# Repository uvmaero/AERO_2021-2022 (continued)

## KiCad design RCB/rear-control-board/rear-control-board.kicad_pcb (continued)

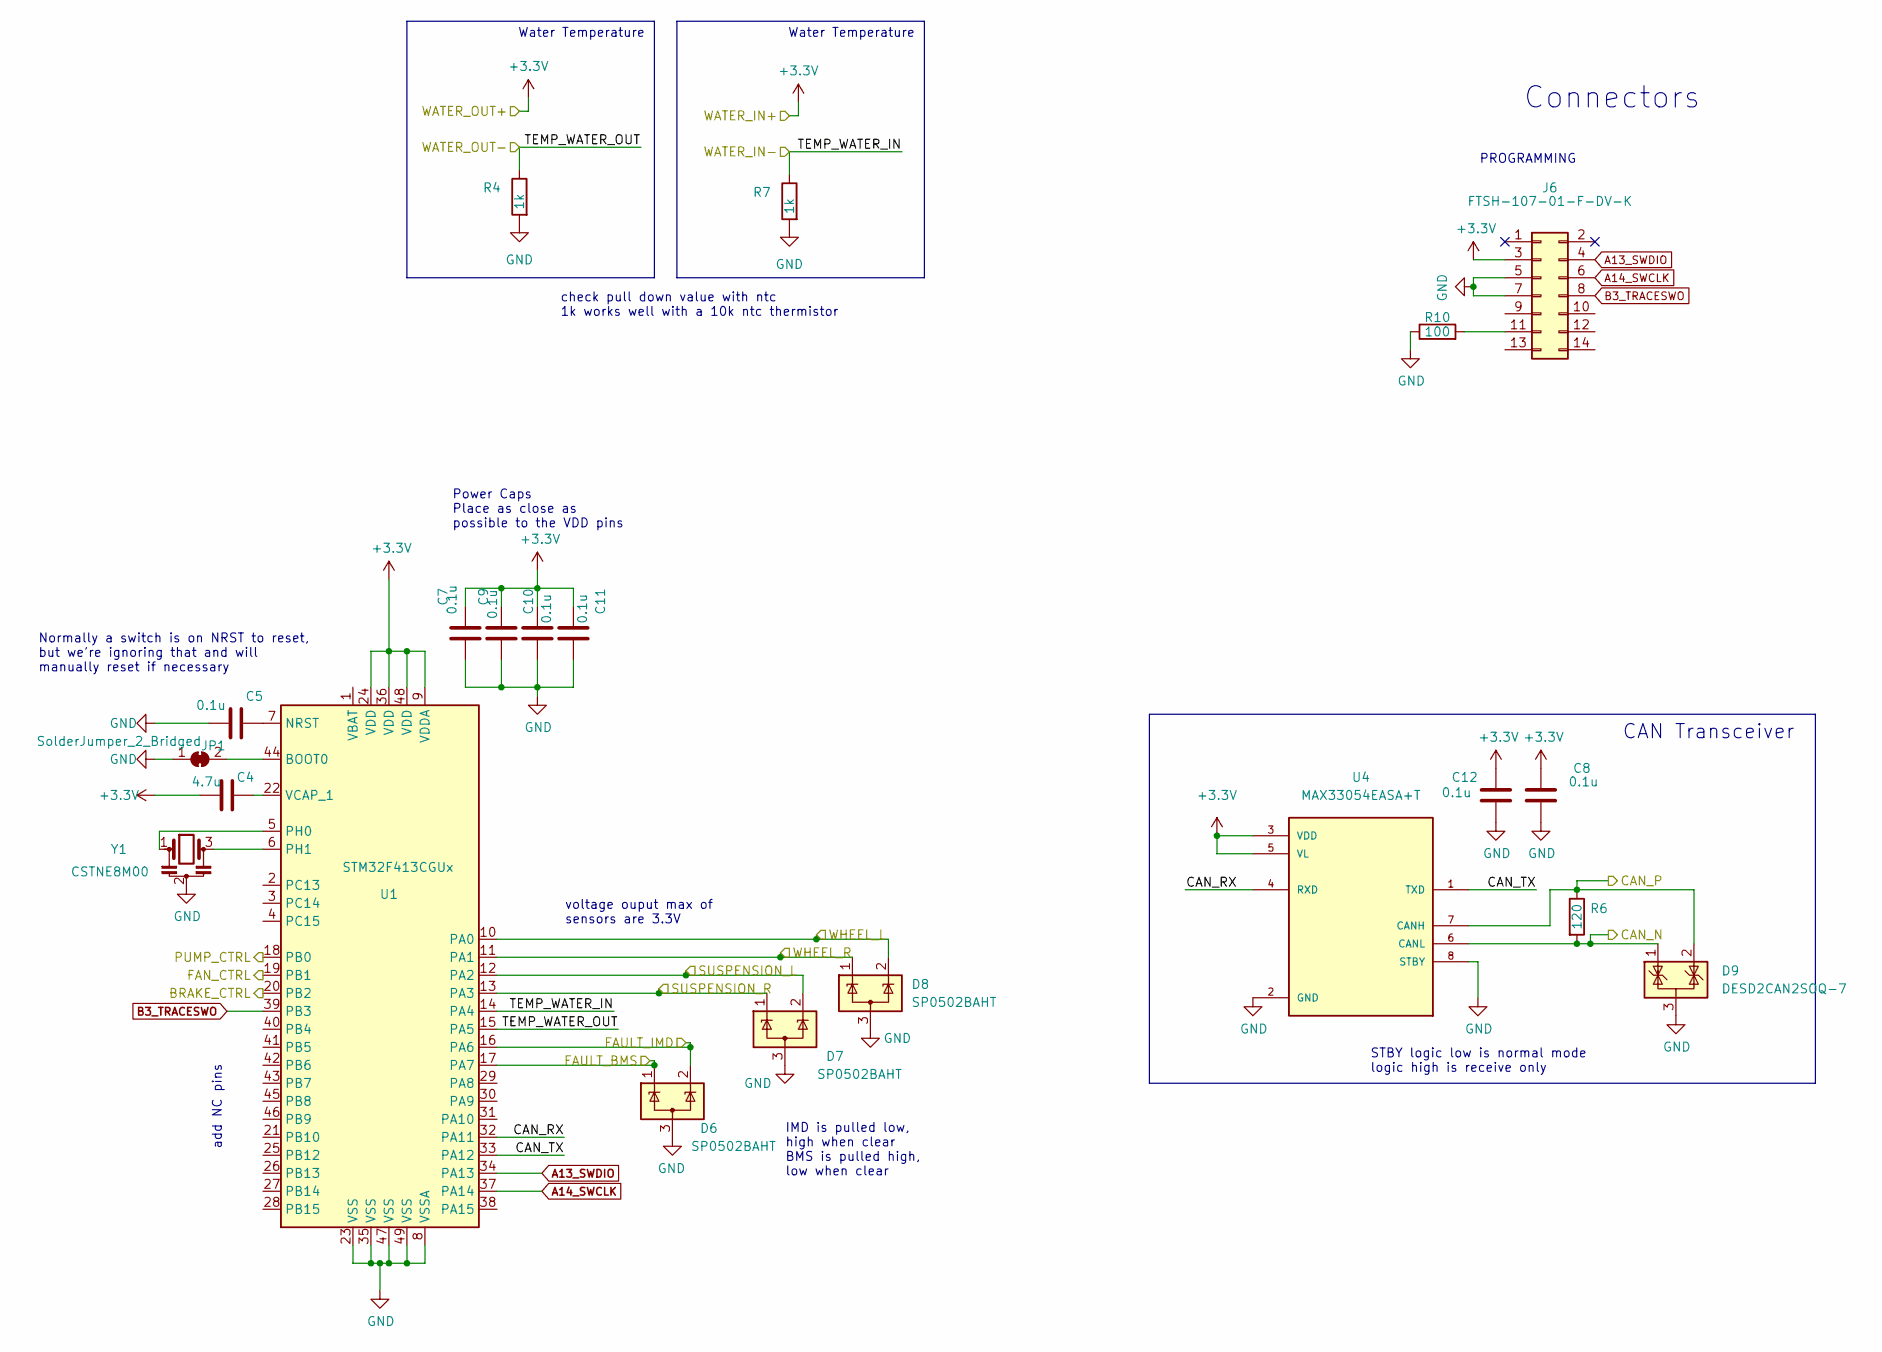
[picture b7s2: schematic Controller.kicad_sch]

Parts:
C4: 4.7u; C_0603_1608Metric_Pad1.08x0.95mm_HandSolder
C5, C7, C8, C9, C10, C11, C12: 0.1u; C_0603_1608Metric_Pad1.08x0.95mm_HandSolder
D6, D7, D8: SP0502BAHT; SOT-23
D9: DESD2CAN2SOQ-7; SOT-23
J6: FTSH-107-01-F-DV-K; PinHeader_2x07_P1.27mm_Vertical_SMD
JP1: SolderJumper_2_Bridged; SolderJumper-2_P1.3mm_Bridged_Pad1.0x1.5mm
R4, R7: 1k; R_0603_1608Metric_Pad0.98x0.95mm_HandSolder
R6: 120; R_0603_1608Metric_Pad0.98x0.95mm_HandSolder
R10: 100; R_0603_1608Metric_Pad0.98x0.95mm_HandSolder
U1: STM32F413CGUx; QFN-48-1EP_7x7mm_P0.5mm_EP5.6x5.6mm
U4: MAX33054EASA+T; SOIC127P600X175-8N
Y1: CSTNE8M00; Resonator_SMD_muRata_CSTxExxV-3Pin_3.0x1.1mm_HandSoldering

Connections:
+3V3: C4.2, C7.1, C8.1, C9.1, C10.1, C11.1, C12.1, J6.3, U1.9 (VDDA), U1.24 (VDD), U1.36 (VDD), U1.48 (VDD), U4.3 (VDD), U4.5 (VL); also elsewhere on the board
/CAN_N: D9.1 (K), R6.2, U4.6 (CANL); also elsewhere on the board
/CAN_P: D9.2 (K), R6.1, U4.7 (CANH); also elsewhere on the board
/Controller/BRAKE_CTRL: U1.20 (PB2); also elsewhere on the board
/Controller/CAN_RX: U1.32 (PA11), U4.4 (RXD)
/Controller/CAN_TX: U1.33 (PA12), U4.1 (TXD)
/Controller/FAN_CTRL: U1.19 (PB1); also elsewhere on the board
/Controller/FAULT_IMD: D6.2 (K), U1.16 (PA6); also elsewhere on the board
/Controller/PUMP_CTRL: U1.18 (PB0); also elsewhere on the board
/FAULT_LATCHER/BMS_SWITCH: D6.1 (K), U1.17 (PA7); also elsewhere on the board
/SUSPENSION_L: D7.2 (K), U1.12 (PA2); also elsewhere on the board
/SUSPENSION_R: D7.1 (K), U1.13 (PA3); also elsewhere on the board
/WATER_IN-: R7.1, U1.14 (PA4); also elsewhere on the board
/WATER_OUT-: R4.1, U1.15 (PA5); also elsewhere on the board
/WHEEL_L: D8.2 (K), U1.10 (PA0); also elsewhere on the board
/WHEEL_R: D8.1 (K), U1.11 (PA1); also elsewhere on the board
A13_SWDIO: J6.4, U1.34 (PA13)
A14_SWCLK: J6.6, U1.37 (PA14)
B3_TRACESWO: J6.8, U1.39 (PB3)
GND: C5.2, C7.2, C8.2, C9.2, C10.2, C11.2, C12.2, D6.3 (A), D7.3 (A), D8.3 (A), D9.3 (A), J6.5, J6.7, JP1.1 (A), R4.2, R7.2, R10.1, U1.8 (VSSA), U1.23 (VSS), U1.35 (VSS), U1.47 (VSS), U1.49 (VSS), U4.2 (GND), U4.8 (STBY), Y1.2; also elsewhere on the board
unnamed: C4.1, U1.22 (VCAP_1)
unnamed: C5.1, U1.7 (NRST)
unnamed: J6.11, R10.2
unnamed: JP1.2 (B), U1.44 (BOOT0)
unnamed: U1.5 (PH0), Y1.1
unnamed: U1.6 (PH1), Y1.3

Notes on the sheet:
Water Temperature
check pull down value with ntc 1k works well with a 10k ntc thermistor
CAN Transceiver
add NC pins
Normally a switch is on NRST to reset, but we're ignoring that and will manually reset if necessary
IMD is pulled low, high when clear BMS is pulled high, low when clear
voltage ouput max of sensors are 3.3V
Connectors
Power Caps Place as close as possible to the VDD pins
STBY logic low is normal mode logic high is receive only
PROGRAMMING

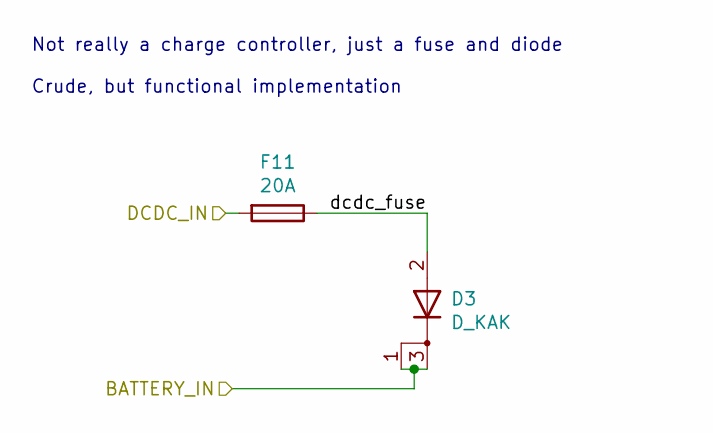
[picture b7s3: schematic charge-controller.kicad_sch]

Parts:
D3: D_KAK; TO-252-2
F11: 20A; Fuseholder_Blade_Mini_Keystone_3568

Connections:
/BATT_12V: D3.1 (K), D3.3 (K); also elsewhere on the board
/DCDC_IN: F11.2; also elsewhere on the board
/charge-controller/dcdc_fuse: D3.2 (A), F11.1

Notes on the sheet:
Not really a charge controller, just a fuse and diode Crude, but functional implementation

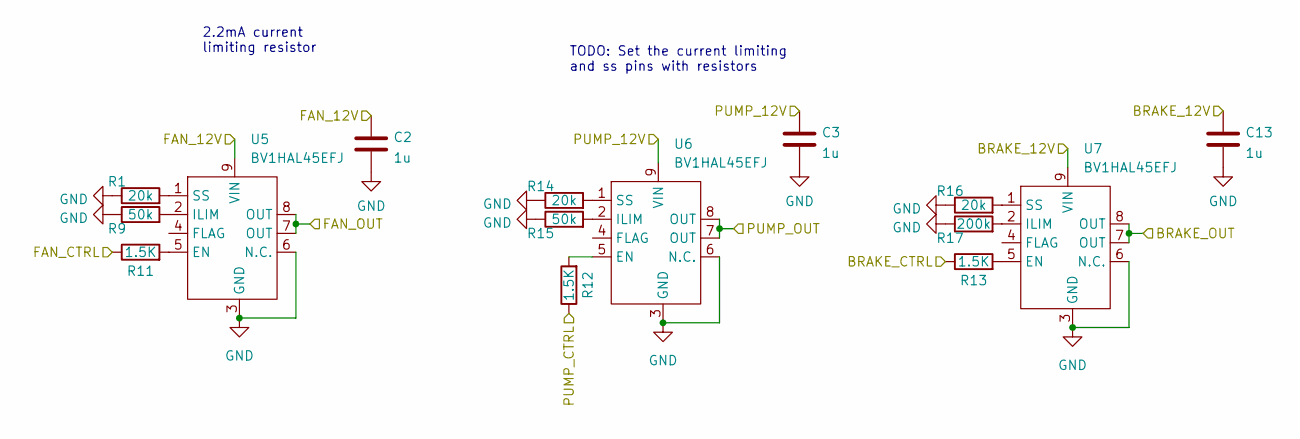
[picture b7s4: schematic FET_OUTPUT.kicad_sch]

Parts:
C2, C3, C13: 1u; C_0603_1608Metric_Pad1.08x0.95mm_HandSolder
R1, R14, R16: 20k; R_0603_1608Metric_Pad0.98x0.95mm_HandSolder
R9, R15: 50k; R_0603_1608Metric_Pad0.98x0.95mm_HandSolder
R11, R12, R13: 1.5K; R_0603_1608Metric_Pad0.98x0.95mm_HandSolder
R17: 200k; R_0603_1608Metric_Pad0.98x0.95mm_HandSolder
U5, U6, U7: BV1HAL45EFJ; HTSOP-8-1EP_3.9x4.9mm_P1.27mm_EP2.4x3.2mm_ThermalVias

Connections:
/BRAKE_12V: C13.1, U7.9 (VIN); also elsewhere on the board
/BRAKE_CTRL_12V: U7.7 (OUT), U7.8 (OUT); also elsewhere on the board
/Controller/BRAKE_CTRL: R13.1; also elsewhere on the board
/Controller/FAN_CTRL: R11.1; also elsewhere on the board
/Controller/PUMP_CTRL: R12.1; also elsewhere on the board
/FAN_12V: C2.1, U5.9 (VIN); also elsewhere on the board
/FAN_CTRL_12V: U5.7 (OUT), U5.8 (OUT); also elsewhere on the board
/PUMP_12V: C3.1, U6.9 (VIN); also elsewhere on the board
/PUMP_CTRL_12V: U6.7 (OUT), U6.8 (OUT); also elsewhere on the board
GND: C2.2, C3.2, C13.2, R1.1, R9.1, R14.1, R15.1, R16.1, R17.1, U5.3 (GND), U5.6 (N.C.), U6.3 (GND), U6.6 (N.C.), U7.3 (GND), U7.6 (N.C.); also elsewhere on the board
unnamed: R11.2, U5.5 (EN)
unnamed: R13.2, U7.5 (EN)
unnamed: R1.2, U5.1 (SS)
unnamed: R9.2, U5.2 (ILIM)
unnamed: R14.2, U6.1 (SS)
unnamed: R15.2, U6.2 (ILIM)
unnamed: R12.2, U6.5 (EN)
unnamed: R16.2, U7.1 (SS)
unnamed: R17.2, U7.2 (ILIM)

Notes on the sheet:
2.2mA current limiting resistor
TODO: Set the current limiting and ss pins with resistors

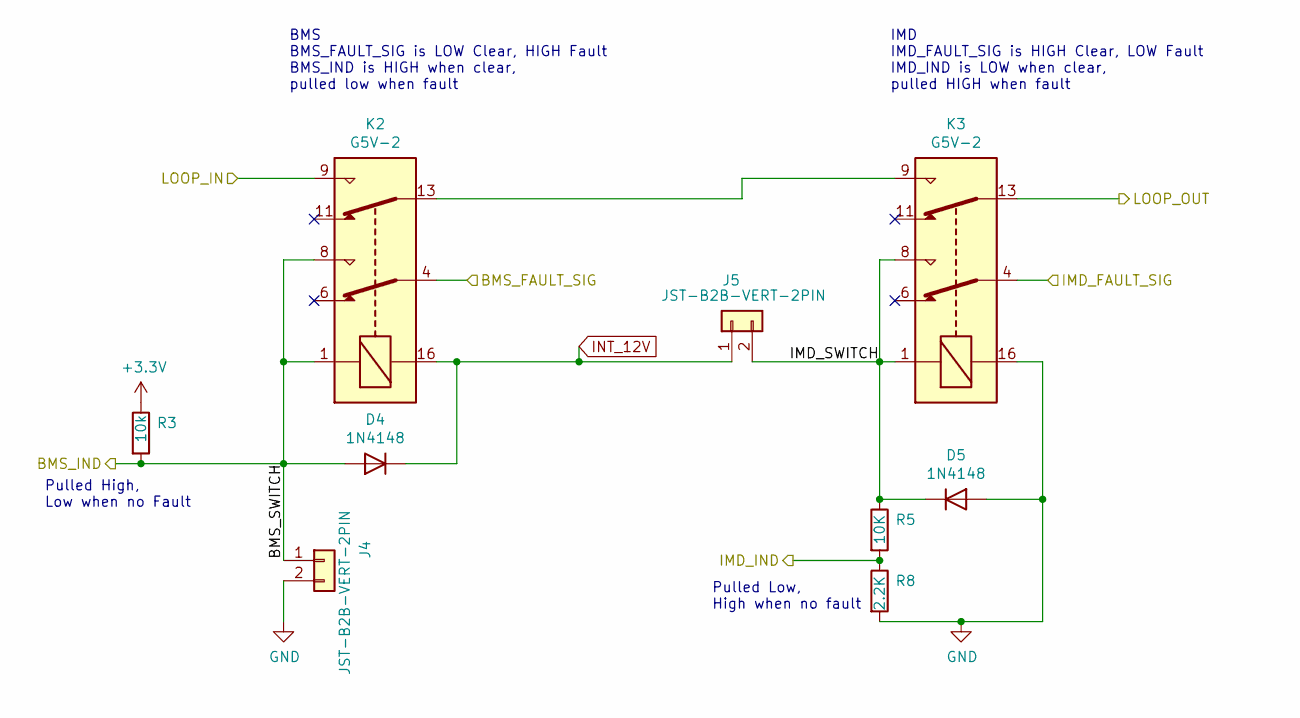
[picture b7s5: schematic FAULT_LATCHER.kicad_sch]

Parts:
D4, D5: 1N4148; D_SOD-123
J4, J5: JST-B2B-VERT-2PIN; JST_XH_B2B-XH-AM_1x02_P2.50mm_Vertical
K2, K3: G5V-2; Relay_DPDT_Omron_G5V-2
R3: 10k; R_0603_1608Metric_Pad0.98x0.95mm_HandSolder
R5: 10K; R_0603_1608Metric_Pad0.98x0.95mm_HandSolder
R8: 2.2K; R_0603_1608Metric_Pad0.98x0.95mm_HandSolder

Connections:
+3V3: R3.1; also elsewhere on the board
/BRB_RTN: K2.9; also elsewhere on the board
/Controller/FAULT_IMD: R5.2, R8.1; also elsewhere on the board
/FAULT_BMS: K2.4; also elsewhere on the board
/FAULT_IMD: K3.4; also elsewhere on the board
/FAULT_LATCHER/BMS_SWITCH: D4.2 (A), J4.1, K2.1, K2.8, R3.2; also elsewhere on the board
/FAULT_LATCHER/IMD_SWITCH: D5.1 (K), J5.2, K3.1, K3.8, R5.1
/SSOK: K3.13; also elsewhere on the board
GND: D5.2 (A), J4.2, K3.16, R8.2; also elsewhere on the board
INT_12V: D4.1 (K), J5.1, K2.16; also elsewhere on the board
unnamed: K2.13, K3.9

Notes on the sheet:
Pulled High, Low when no Fault
IMD IMD_FAULT_SIG is HIGH Clear, LOW Fault IMD_IND is LOW when clear, pulled HIGH when fault
Pulled Low, High when no fault
BMS BMS_FAULT_SIG is LOW Clear, HIGH Fault BMS_IND is HIGH when clear, pulled low when fault

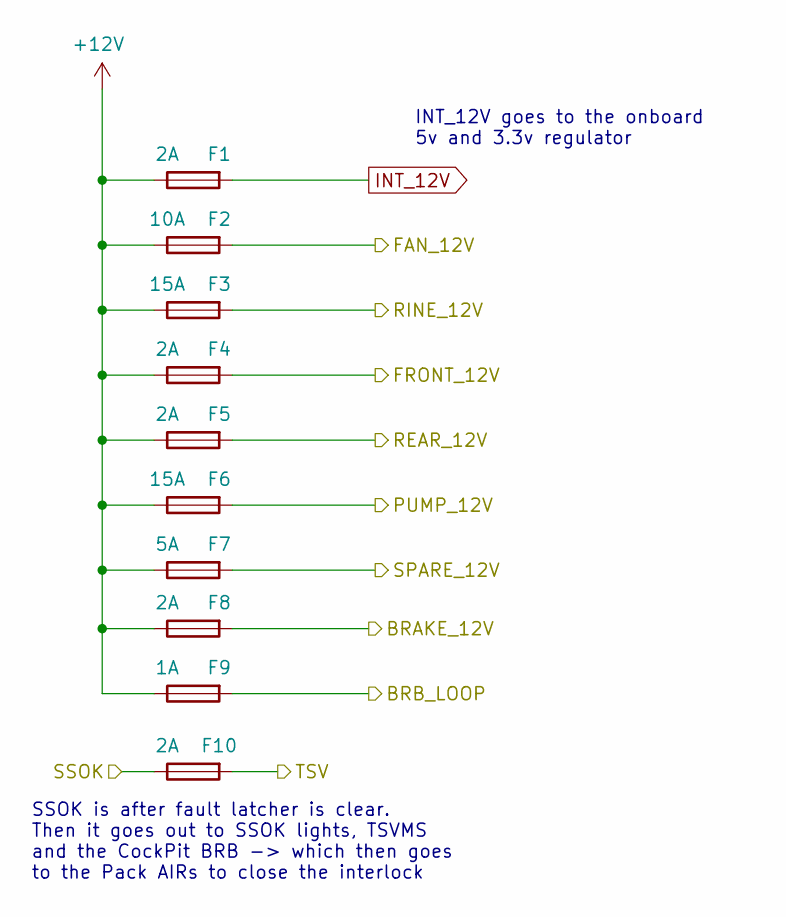
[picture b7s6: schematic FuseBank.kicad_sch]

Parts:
F1, F4, F5, F8, F10: 2A; Fuseholder_Blade_Mini_Keystone_3568
F2: 10A; Fuseholder_Blade_Mini_Keystone_3568
F3, F6: 15A; Fuseholder_Blade_Mini_Keystone_3568
F7: 5A; Fuseholder_Blade_Mini_Keystone_3568
F9: 1A; Fuseholder_Blade_Mini_Keystone_3568

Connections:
+12V: F1.1, F2.1, F3.1, F4.1, F5.1, F6.1, F7.1, F8.1, F9.1; also elsewhere on the board
/BRAKE_12V: F8.2; also elsewhere on the board
/FAN_12V: F2.2; also elsewhere on the board
/FuseBank/BRB_LOOP: F9.2; also elsewhere on the board
/FuseBank/FRONT_12V: F4.2; also elsewhere on the board
/FuseBank/RINE_12V: F3.2; also elsewhere on the board
/FuseBank/SPARE_12V: F7.2; also elsewhere on the board
/FuseBank/TSV: F10.2; also elsewhere on the board
/PUMP_12V: F6.2; also elsewhere on the board
/REAR_12V: F5.2; also elsewhere on the board
/SSOK: F10.1; also elsewhere on the board
INT_12V: F1.2; also elsewhere on the board

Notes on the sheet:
SSOK is after fault latcher is clear. Then it goes out to SSOK lights, TSVMS and the CockPit BRB -> which then goes to the Pack AIRs to close the interlock
INT_12V goes to the onboard 5v and 3.3v regulator

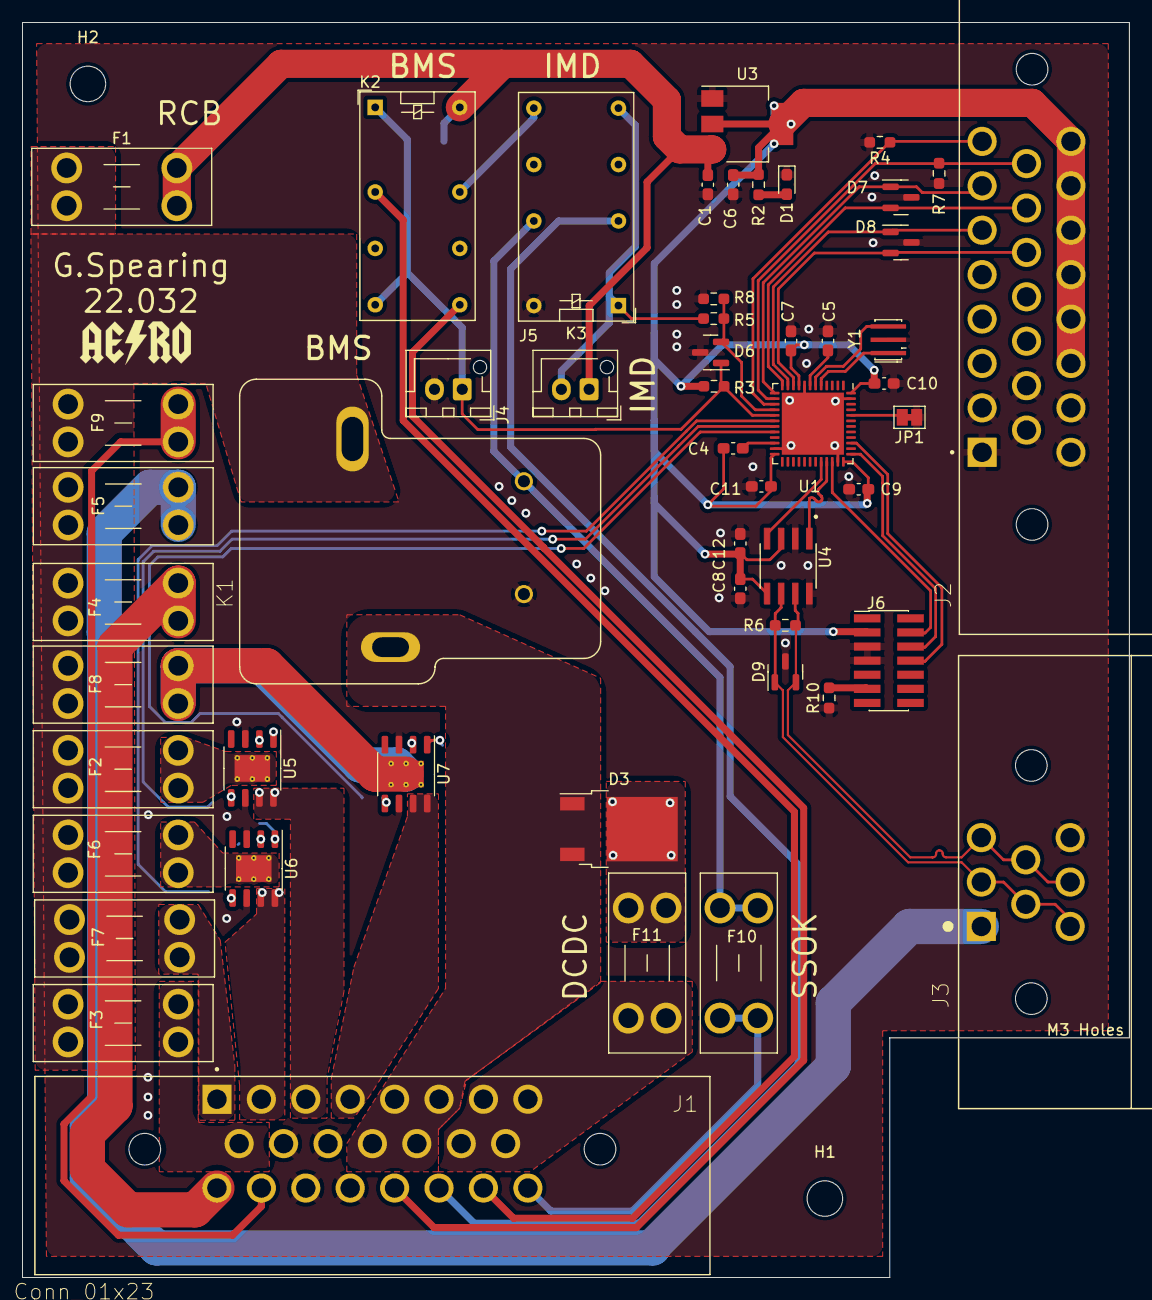
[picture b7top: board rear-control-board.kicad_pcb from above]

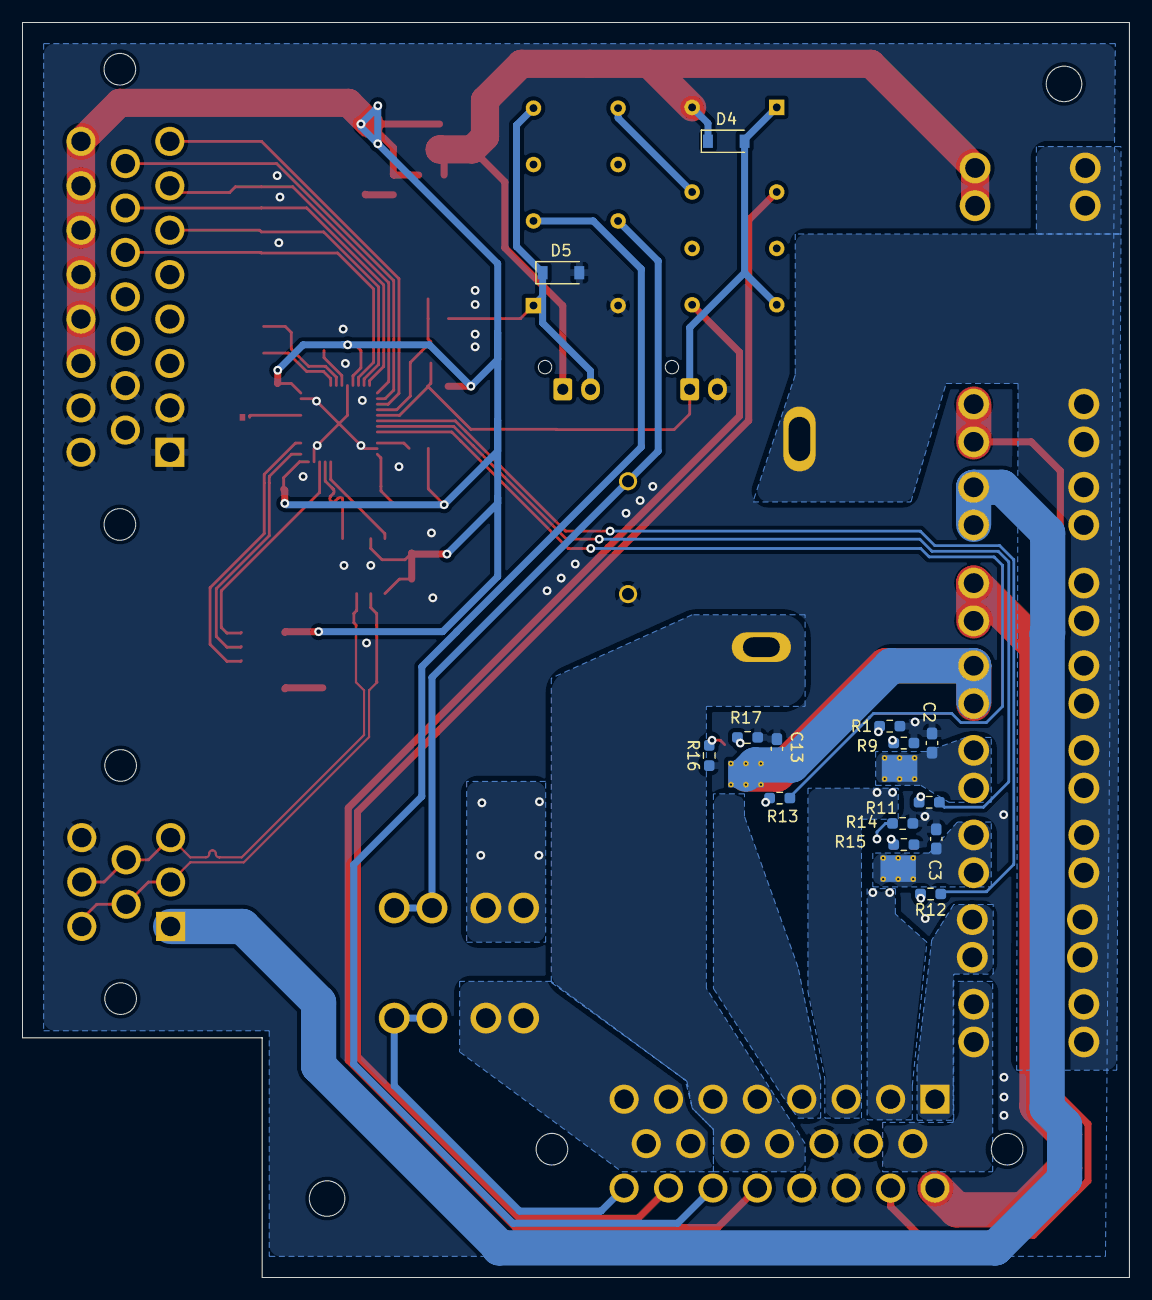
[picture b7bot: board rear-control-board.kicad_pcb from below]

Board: 2 copper layers, 99.7 x 113.0 mm, 68 parts (14 on the bottom side), 59 nets.

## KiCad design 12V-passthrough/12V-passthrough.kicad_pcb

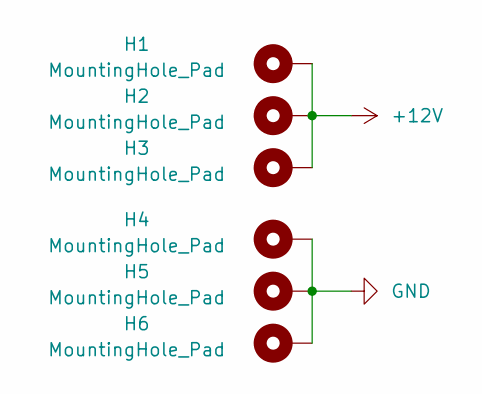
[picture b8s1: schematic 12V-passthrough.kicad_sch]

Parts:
H1, H2, H3, H4, H5, H6: MountingHole_Pad; MountingHole_2.2mm_M2_ISO14580_Pad_TopBottom

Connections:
+12V: H1.1, H2.1, H3.1
GND: H4.1, H5.1, H6.1

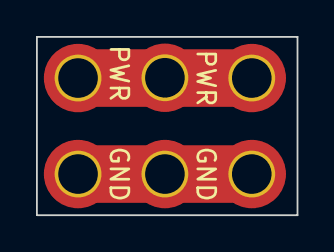
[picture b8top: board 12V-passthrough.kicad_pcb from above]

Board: 2 copper layers, 14.5 x 9.9 mm, 6 parts (0 on the bottom side), 2 nets.

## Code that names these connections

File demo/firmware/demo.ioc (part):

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Mcu.Name=STM32F413C(G-H)Ux
Mcu.Package=UFQFPN48
Mcu.UserName=STM32F413CGUx
PA0.Signal=ADCx_IN0
PA1.Signal=ADCx_IN1
PA10.Signal=GPIO_Output
PA11.Mode=CAN_Activate
PA11.Signal=CAN1_RX
PA12.Mode=CAN_Activate
PA12.Signal=CAN1_TX
PA13.Mode=Serial_Wire
PA13.Signal=SYS_JTMS-SWDIO
PA14.Mode=Serial_Wire
PA14.Signal=SYS_JTCK-SWCLK
PA2.Signal=ADCx_IN2
PA3.Signal=ADCx_IN3
PA4.Signal=ADCx_IN4
PA5.Signal=ADCx_IN5
PA6.Signal=ADCx_IN6
PA7.Signal=ADCx_IN7
PB0.Signal=ADCx_IN8
PB1.Signal=ADCx_IN9
PH0\ -\ OSC_IN.Signal=RCC_OSC_IN
PH1\ -\ OSC_OUT.Signal=RCC_OSC_OUT
RCC.SYSCLKFreq_VALUE=100000000
RCC.SYSCLKSource=RCC_SYSCLKSOURCE_PLLCLK
board=custom

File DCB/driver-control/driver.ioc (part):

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Mcu.Name=STM32F413C(G-H)Ux
Mcu.Package=UFQFPN48
Mcu.UserName=STM32F413CGUx
PA10.Signal=GPIO_Output
PA11.Mode=CAN_Activate
PA11.Signal=CAN1_RX
PA12.Mode=CAN_Activate
PA12.Signal=CAN1_TX
PA13.Mode=Serial_Wire
PA13.Signal=SYS_JTMS-SWDIO
PA14.Mode=Serial_Wire
PA14.Signal=SYS_JTCK-SWCLK
PA4.Signal=ADCx_IN4
PA5.Signal=ADCx_IN5
PA6.Signal=ADCx_IN6
PA7.Signal=ADCx_IN7
PB10.Signal=GPIO_Output
PB12.Signal=GPIO_Input
PB13.Signal=GPIO_Input
PB15.Signal=GPIO_Input
PB2.Signal=GPIO_Output
PB8.Signal=GPIO_Output
PH0\ -\ OSC_IN.Mode=HSE-External-Oscillator
PH0\ -\ OSC_IN.Signal=RCC_OSC_IN
PH1\ -\ OSC_OUT.Mode=HSE-External-Oscillator
PH1\ -\ OSC_OUT.Signal=RCC_OSC_OUT
RCC.SYSCLKFreq_VALUE=90000000
RCC.SYSCLKSource=RCC_SYSCLKSOURCE_PLLCLK
board=custom

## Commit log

2021-10-19 Create test
2021-10-19 adding file organization structure
2021-10-19 Adding board layout and descriptions
2021-11-10 initializing board and firmware
2021-11-16 initializing project files
    - create hardware schematic for dev board (with CAN)
    - create CubeIDE project and assign a few pins (empty code)
2021-12-03 removing demo, it's now it's own repo
2021-12-03 adding new names for boards
2021-12-04 merging the demo board back in
2021-12-04 updating file location
2021-12-04 initializing folders for projects
2022-01-19 cleaning up folders
2022-01-19 initializing KiCad projects
2022-01-20 creating schematic for RCB
2022-01-22 in progress schematic
2022-01-22 append HV schematics from old files
2022-01-22 finish schematic, start layout
2022-01-22 working on layout
2022-01-22 working on schematic
2022-01-22 layout and connector pins
2022-01-22 changing connector pinout
2022-01-24 updating to new kicad version
2022-01-25 working on layout for boards
    HVB and PAM layouts. Also updating files to new kicad version
2022-01-26 working on layout
    Updating traces for RCB and organizing HVB
2022-01-26 adding documentation outlines
2022-01-26 adding resolver project
    initialized project
2022-01-26 adding bms pass through board
    initializing BPB project
2022-01-26 updating board layout
2022-01-26 updating trace layout
2022-01-26 adding traces
2022-01-26 updated tutorial
2022-01-27 starting layout
2022-01-27 updating hv layout
2022-01-28 initializing stm32 project files
2022-01-28 started defines and commenting code structure
2022-01-28 ignore kicad backup files
2022-01-29 DCB Layout Rev 1 Complete
    Complete the layout first draft
2022-01-29 Adding silkscreen text
2022-01-29 almost done with layout
    HV layout almost done. Tracing
2022-01-30 finishing layout placement
    Still need to route wires
2022-01-30 updating pcb size and layout
2022-01-30 updating pinout on one connector
2022-01-30 removing cached files
2022-01-30 adding corner cutout and updating layout
2022-01-30 adjusting pinout, updating layout
2022-01-30 Layout Trace Complete
    completed layout of tracks. Still need to place silkscreens
2022-01-30 updating trace correction temp
    changing trace and pinout of a temp wire
2022-01-30 trace layout complete (need review)
2022-01-30 updating pinout
2022-01-30 removing cached kicad backups
2022-01-30 autosave files from kicad closing
2022-01-30 adding mounting holes
2022-01-31 removing old backup files from cache
2022-01-31 ignore vscode settings
2022-01-31 updating power filtering
2022-01-31 power filtering and notes
2022-01-31 updating filtering cap layout
    Kay suggested layout changes. Moved caps around
2022-02-01 finished assigning pins
2022-02-01 finished defining pins
2022-02-01 some precharge stuff
2022-02-01 precharge switch and rtd button
2022-02-01 defines
2022-02-01 fixed formatting
2022-02-01 formatting
2022-02-01 even more precharge
2022-02-01 even even more precharge :)
2022-02-01 lcd stuff
2022-02-01 more lcd stuff
2022-02-01 updated lcd code from arduino lib to stm32 lib
2022-02-01 finished preset LCD screens for displaying relevant car data
2022-02-01 just dumb formatting that was bothering from from the last commit
2022-02-01 added lcd_clear()s where needed
2022-02-01 formatting with jorge
2022-02-01 finished footprint
2022-02-01 test push
2022-02-01 DRC and Labeling Complete
2022-02-01 Added comments to layout future code.
2022-02-01 test
2022-02-02 Add files via upload
    emrack pcb
2022-02-02 DRC updating
2022-02-02 put files in folder
2022-02-02 DRC and layout update
2022-02-02 ignoring backup files and other settings
2022-02-02 updating emrax board location
2022-02-02 initial emrax board design
2022-02-02 initial 12V board layout
2022-02-02 board notes for willem
2022-02-02 moved precharge stuff to HVB
2022-02-02 added calculations for LCD values
2022-02-02 initializing pacman side 2 file
2022-02-02 merging interface board from main
2022-02-02 review of boards
2022-02-02 removing backup files
2022-02-02 5mm Led changed
2022-02-02 Documentation for ESF2
2022-02-02 Cleaned up
2022-02-02 updating side 2 mirror
2022-02-02 added battery
2022-02-02 updating footprint and 3d model links
2022-02-03 finish layout and labeling
2022-02-03 layout and labeling update
2022-02-03 Layout and Footprints update
2022-02-03 update layout and labeling
2022-02-03 update board step model
2022-02-03 updating step model with connectors
2022-02-03 updating can pinouts
2022-02-03 Update layout with more connectors
    Added passthrough for BMS
2022-02-04 Adding CAN termination resistors
2022-02-04 updating silkscreen objects
2022-02-04 Adding images for TSV/GVL demonstrations
2022-02-04 added more images of boards
2022-02-04 removing cached backups
2022-02-04 working on file
2022-02-04 finished battery schematic and saftey loop
    finished battery schematic and saftey loop
2022-02-05 removing old board files
2022-02-05 generating BOMs
2022-02-06 updating board review BOM with notes
2022-02-06 start to interface with all surface mounted parts
2022-02-06 Major Review and Part Update
    updating footprints, component values, layouts
2022-02-08 added CAN stuff!
2022-02-08 formatting and suspension stuff
2022-02-08 squashing bugs!
2022-02-08 squashing more bugs! :)
2022-02-08 squashing even more bugs :) - dom
2022-02-08 squashing more bugs! -dom
2022-02-08 implementing the actual stuff for analog reads
2022-02-08 grrrrr adc reads
2022-02-08 board formatting
2022-02-08 uncommenting stuff
2022-02-08 updating pinouts
2022-02-09 working on dcb - nothing works
    @dom-gasperini is doing things. WTF is going on?
2022-02-09 updating labels
2022-02-09 updating demo board
2022-02-09 willem review notes
2022-02-10 updating emrax breakout board
2022-02-10 adding CAD and changing programming on HVB
2022-02-10 updating demo schem
2022-02-10 updating schem with design notes (major changes)
2022-02-10 ignoring autosave files
2022-02-10 restarted dash and now its better and works
2022-02-10 formatting :)
2022-02-10 wheel diameter question has been answered
2022-02-10 more formatting
2022-02-10 even even more formatting
2022-02-10 minor changes, dont worry about it ;)
2022-02-10 just more dumb fomatting
2022-02-10 added TODO
2022-02-10 added new can send ids and their message contents
2022-02-10 minor layout changes based on schem updates
2022-02-10 lcd selective clearing for faster screen updates
2022-02-10 making the display do fancy things
2022-02-11 updating layout with schem changes
2022-02-11 did the thing it's done
2022-02-11 i lied, not done, still need to read can
2022-02-12 working on reading can mesages
2022-02-12 updating schematic based on RCB changes
2022-02-12 working on demo board, schem done
2022-02-12 layout finished (need to place silkscreens)
2022-02-12 updating schem and layout. WIP
2022-02-12 finished demo board schem and layout
2022-02-14 finished schem and layout. Ready for Review
2022-02-14 finishing layout and labels
2022-02-14 updating layout and minor schem updates
2022-02-14 finish layout ready for review
2022-02-14 change schem and finish layout Ready for Review
2022-02-14 updating layout notes
2022-02-14 touching up layout and making gerbers
2022-02-14 updating step models
2022-02-14 top of file description
2022-02-16 setting up the RCB .ioc file
2022-02-16 its all messed up :(((
2022-02-16 Revert "working on reading can mesages"
    This reverts commit 746b767ec8cc34b85295f4e2aab101b800ebb6c7.
2022-02-16 mostly done with driver now
2022-02-16 forgot to push the driver CubeIDE files
2022-02-16 ayo makin makin bacon (mostly finished RCB)
2022-02-16 mostly finished RCB
2022-02-16 another mostly finished RCB
2022-02-16 formatting and finished pollSensorData()
2022-02-16 auto code generation messes with my adc comments
2022-02-16 while loop borked itself so i put it back
2022-02-17 initializing Telemetry files
2022-02-17 removed telementry and created own repo
2022-02-17 missing CAN reads, & need to finish precharge
2022-02-17 worked on precharge stuff
2022-02-17 missing CAN read & worked on precharge, it builds!
2022-02-17 added rinehart can read
2022-02-17 added bms can reads
2022-02-17 missed a semicolon...
2022-02-17 added can reads for brake light & cooling
2022-02-17 can stuff i forgot to add
2022-02-17 added can reads from RCB
2022-02-17 added can reads from HVB
2022-03-06 working on documentation
2022-03-06 seeing how it looks
2022-03-06 the formatting has improved
2022-03-06 added stuff
2022-03-06 can stuff for dash
2022-03-15 defined a function twice by mistake
2022-03-15 debug files
2022-03-15 added more documentaion
2022-03-23 testing can
2022-03-23 updating can config to the working settings
2022-03-24 enabled CAN auto-wake up so now CAN works
2022-03-24 enabled CAN auto wake-up so now it works
2022-03-25 fixed freertos issue & see CAN TODO @ line 206
2022-03-25 fixed CAN address formatting & CAN bank #s
2022-03-27 file reorganization
2022-03-27 minor notes and changes
2022-03-28 switched from adc polling to dma
2022-03-28 fomatting & fixed some dma stuff
2022-03-28 formatting & fixing dma stuff
2022-04-01 minor updates
2022-04-04 building
2022-04-04 CAN and Interupts working
2022-04-05 adding message breakdown
2022-04-06 merging all the code + board designs
2022-04-07 Surface mount dash
2022-04-07 design changes for testbench
2022-04-07 formatting & setup
2022-04-07 trying to update DMA reading
2022-04-08 added buzzer logic
2022-04-08 formatting & more buzzer logic
2022-04-08 added start button interrupt handler
2022-04-08 IRQ handler function prototype for start button
2022-04-08 enable inverter command for rinehart
2022-04-08 uncommented some interrupt stuff
2022-04-11 re-wrote everything and now it works
2022-04-11 updating addresses
2022-04-11 added comments
2022-04-12 start button LED & fixed IMD fault LED bug
2022-04-12 fixed flipped bit LED bug
2022-04-13 Revert "fixed flipped bit LED bug"
    This reverts commit 6415d42a2b260cc07f7e59d0e685321f98522efd.
2022-04-13 added drive modes, added torque remapping
2022-04-13 added some comments and removed an unused variable
2022-04-16 CAN works for now
2022-04-16 CAN and RTD Buzzer works
2022-04-22 updated rinehart command parameter message
2022-04-29 update to Orion BMS message
2022-04-29 fixed dcb can torque message
2022-04-30 updating code for pedal control
2022-04-30 fixed deadband, and simplified some other stuff
2022-05-01 final changes! brake light, DAQ msg, new adc avg
2022-05-01 comments, and improved varible name consistency
2022-05-01 added comments and updated BMS CAN address
2022-05-01 fixed torque ranges
2022-05-01 maybe fixed can address issue
2022-05-01 precharge fix
2022-05-01 make file changes
2022-05-02 Addded comments
2022-05-02 battery car schematic
2022-05-02 updating can interface and comments
2022-05-11 moving all controls to DCB, removing HVB
